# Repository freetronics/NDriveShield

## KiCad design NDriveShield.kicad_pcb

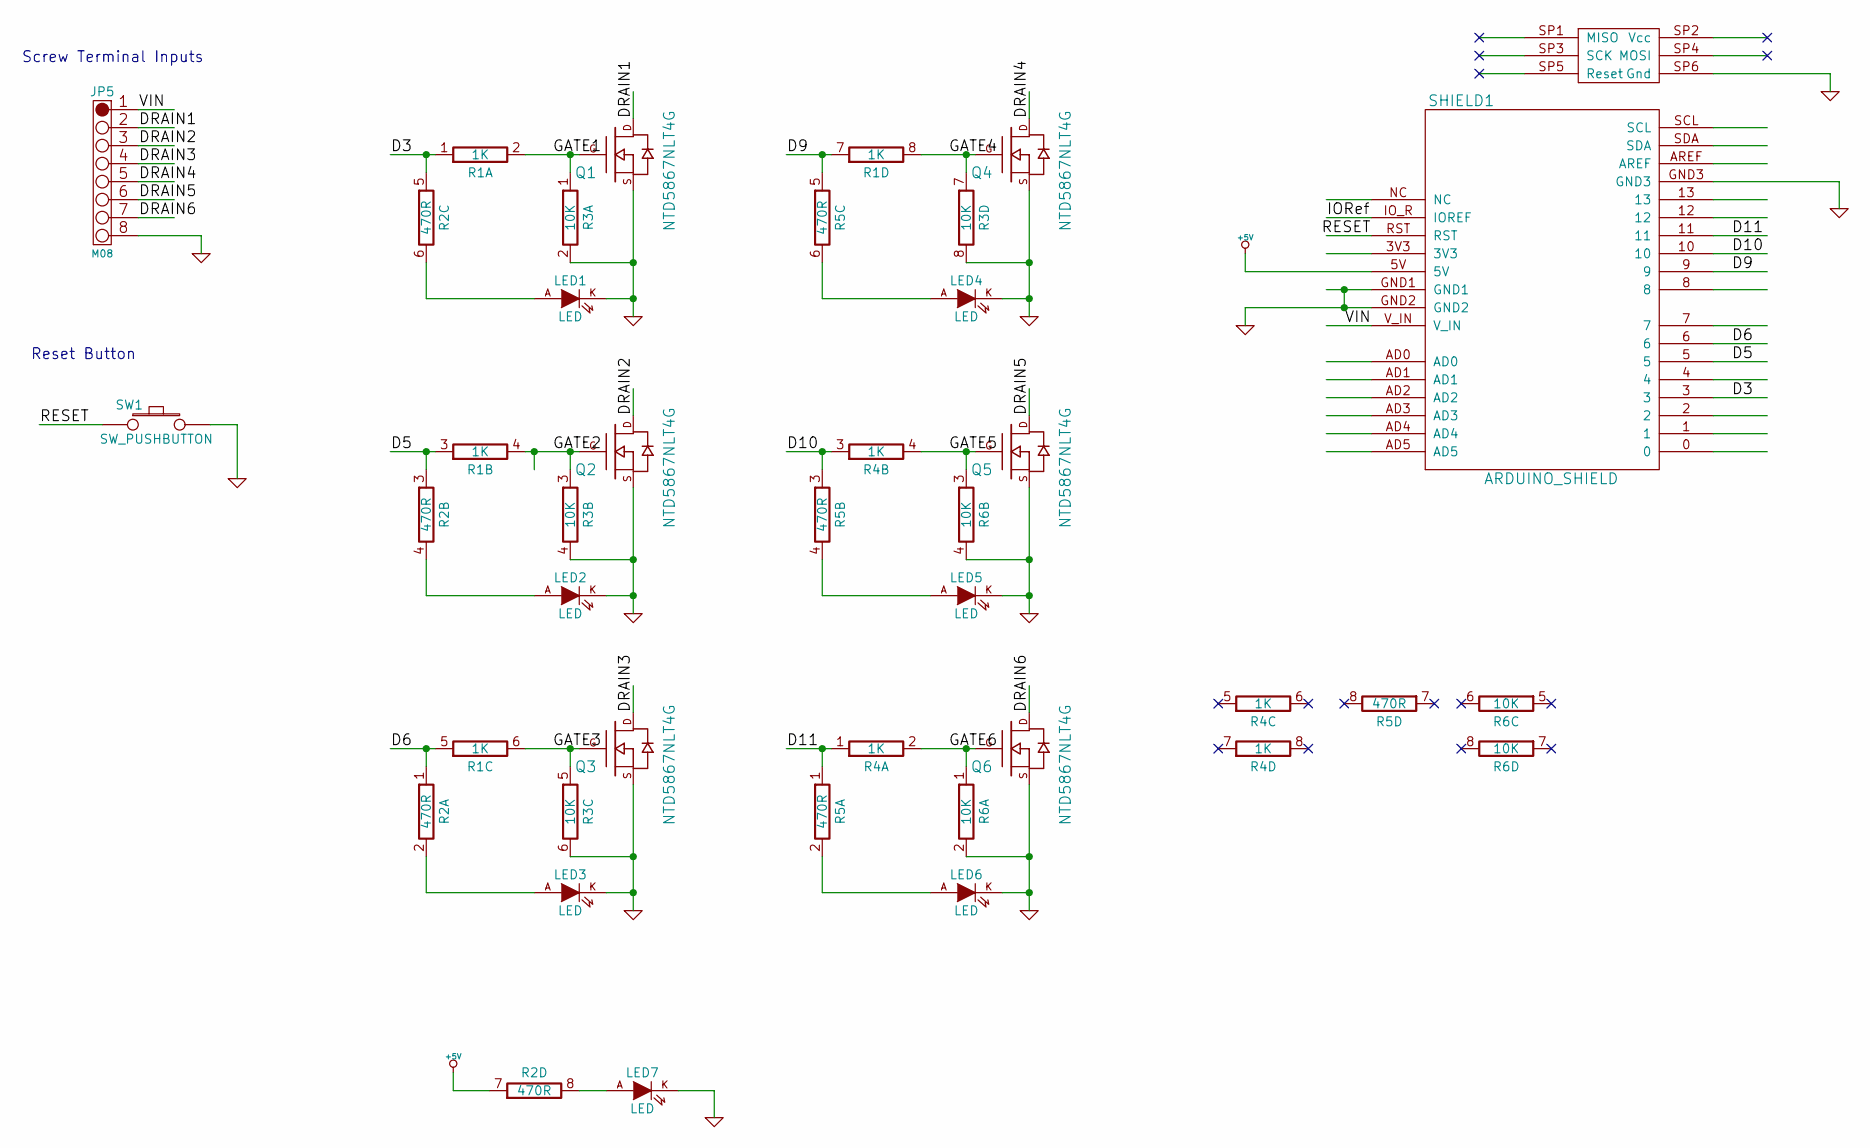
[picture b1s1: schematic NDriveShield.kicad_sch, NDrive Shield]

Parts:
JP5: M08; TERMINALBLOCK_3.5MM_8
LED1, LED2, LED3, LED4, LED5, LED6, LED7: LED; LED-0603
Q1, Q2, Q3, Q4, Q5, Q6: NTD5867NLT4G; MOSFET_DPAK
R1, R4: 1K; RES_CAY16
R2, R5: 470R; RES_CAY16
R3, R6: 10K; RES_CAY16
SHIELD1: ARDUINO_SHIELD; ARDUINO_SHIELD_ROUNDPADS_BREAKOUT
SW1: SW_PUSHBUTTON; TACTILE_SWITCH_SMD_2PIN_TINY

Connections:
+5V: R2.7, SHIELD1.5V
/D3: R1.1 (7), R2.5 (7), SHIELD1.3
/D5: R1.3 (7), R2.3 (7), SHIELD1.5
/D6: R1.5 (7), R2.1 (7), SHIELD1.6
/D9: R1.7, R5.5 (7), SHIELD1.9
/D10: R4.3 (7), R5.3 (7), SHIELD1.10
/D11: R4.1 (7), R5.1 (7), SHIELD1.11
/DRAIN1: JP5.2, Q1.D
/DRAIN2: JP5.3, Q2.D
/DRAIN3: JP5.4, Q3.D
/DRAIN4: JP5.5, Q4.D
/DRAIN5: JP5.6, Q5.D
/DRAIN6: JP5.7, Q6.D
/GATE1: Q1.G, R1.2 (8), R3.1 (7)
/GATE2: Q2.G, R1.4 (8), R3.3 (7)
/GATE3: Q3.G, R1.6 (8), R3.5 (7)
/GATE4: Q4.G, R1.8, R3.7
/GATE5: Q5.G, R4.4 (8), R6.3 (7)
/GATE6: Q6.G, R4.2 (8), R6.1 (7)
/IORef: SHIELD1.IO_R (IOREF)
/RESET: SHIELD1.RST, SW1.1
/VIN: JP5.1, SHIELD1.V_IN
GND: JP5.8, LED1.K, LED2.K, LED3.K, LED4.K, LED5.K, LED6.K, LED7.K, Q1.S, Q2.S, Q3.S, Q4.S, Q5.S, Q6.S, R3.2 (8), R3.4 (8), R3.6 (8), R3.8, R6.2 (8), R6.4 (8), SHIELD1.GND1, SHIELD1.GND2, SHIELD1.GND3, SHIELD1.SP6 (Gnd), SW1.2
unnamed: LED1.A, R2.6 (8)
unnamed: LED2.A, R2.4 (8)
unnamed: LED3.A, R2.2 (8)
unnamed: LED4.A, R5.6 (8)
unnamed: LED5.A, R5.4 (8)
unnamed: LED6.A, R5.2 (8)
unnamed: LED7.A, R2.8

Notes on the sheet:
Screw Terminal Inputs
Reset Button

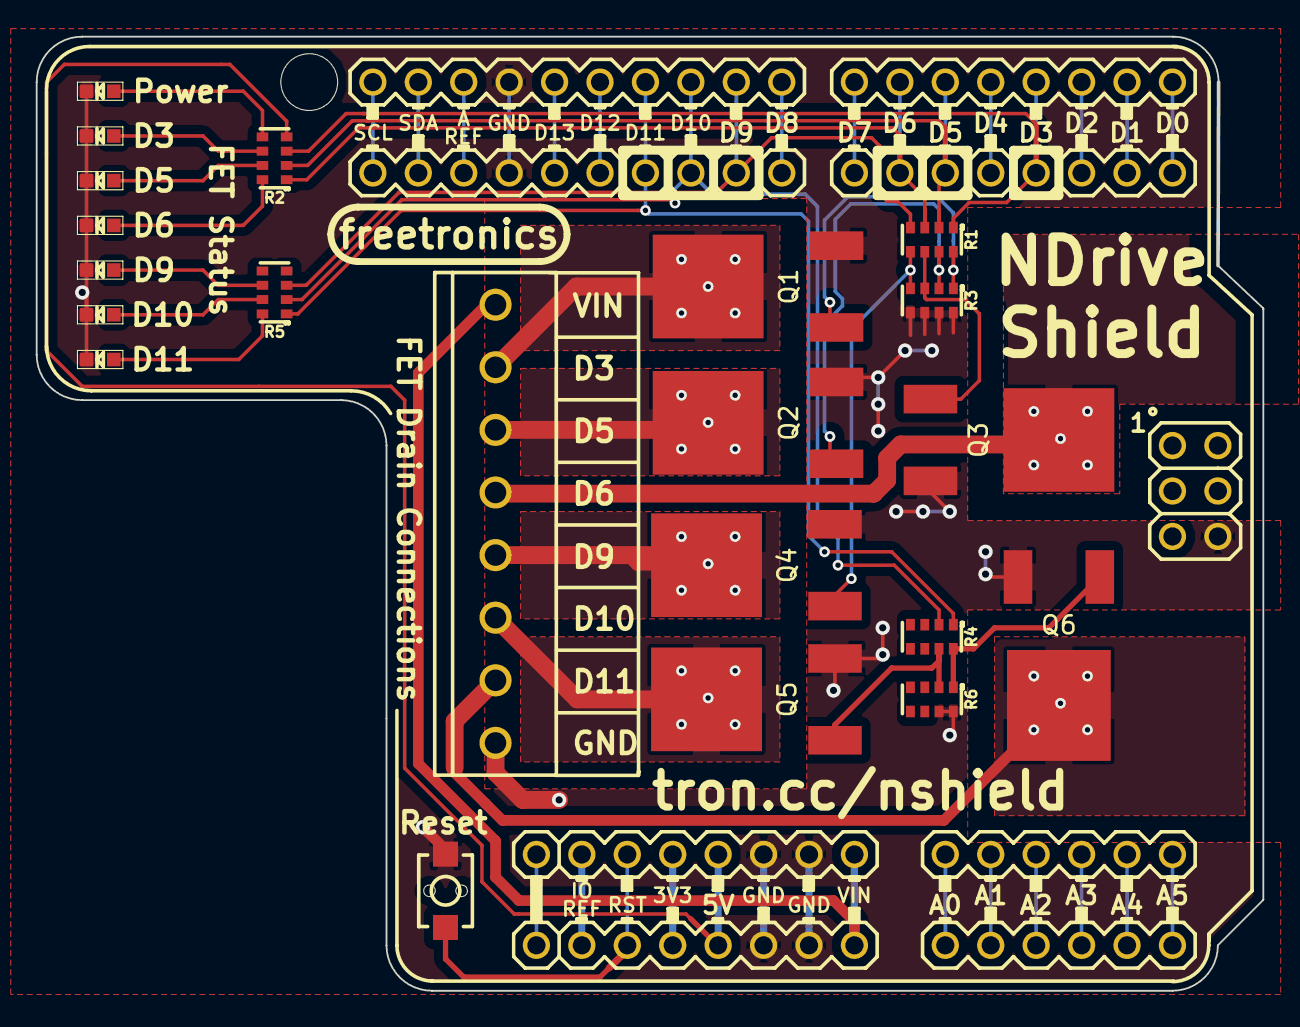
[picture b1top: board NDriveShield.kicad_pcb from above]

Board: 2 copper layers, 68.5 x 53.2 mm, 23 parts (0 on the bottom side), 29 nets.

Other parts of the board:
LOGO_FREETRONICS: val**; LOGO_FREETRONICS

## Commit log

2014-07-10 Initial commit, initial schematic
2014-07-10 Draft layout 1
2014-08-07 NDriveShield first prototype v0.1
2014-08-28 Layout cleanup, fix EtherTen/Mega/Due jack clearance, update to V1.0
2015-05-05 Clean up exposed copper fill areas on bottom of board
2015-05-12 Bump to V1.1, change appearance to FT-style breakout pads.
    Closes #2
2015-05-12 Add borders around output terminal labels
    Closes #3
2021-01-01 #4 Make compatible to KiCAD nightly

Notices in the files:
NDriveShield.kicad_sch:
TAPR Open Hardware License
(C) 2014 Freetronics Pty Ltd
